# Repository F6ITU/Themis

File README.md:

# Themis

A simple directional coupler

This coupler is based on a "tandem match" design with input compensation capacitor.
 
It should be able to fit any kind of amplifier, from 10 to 150 W

The pcb itself  supports the 2 main toroids of the transformer, input and output coax connectors 
and two coupled outputs.

These outputs are followed by a dual detector located on each branch of the coupler. The detected voltage 
is buffered by a dual rail to rail op amp. The output of the operational amplifier is then 
lowered by a resistive divider that keeps each output below the maximum input voltage of Angelia's ADC 

A optional "raw" FWD output is dedicated to the predistorsion -aka pure signal- feedback

3 different versions have been designed so far : V 1.0 was operational but the design and routing were absolutely ugly, with a crazy stripe-line trace.
V2.0 was a real enhancement of the general design (straight microstrip, simpler shielding). V2.1 offers now some small cleaning of the general design
(pure signal output located on the bottom layer, transformer junction also fixed on the bottom layer, thus enhancing the general insulation and 
offering a slightly better directivity. The attenuator of the P.S. output has a better access, thus simplifying the modification of it's value. 

V2.1 is the master branch since March 1st, 2019, and will stay "as is" as long as a new design is pushed.

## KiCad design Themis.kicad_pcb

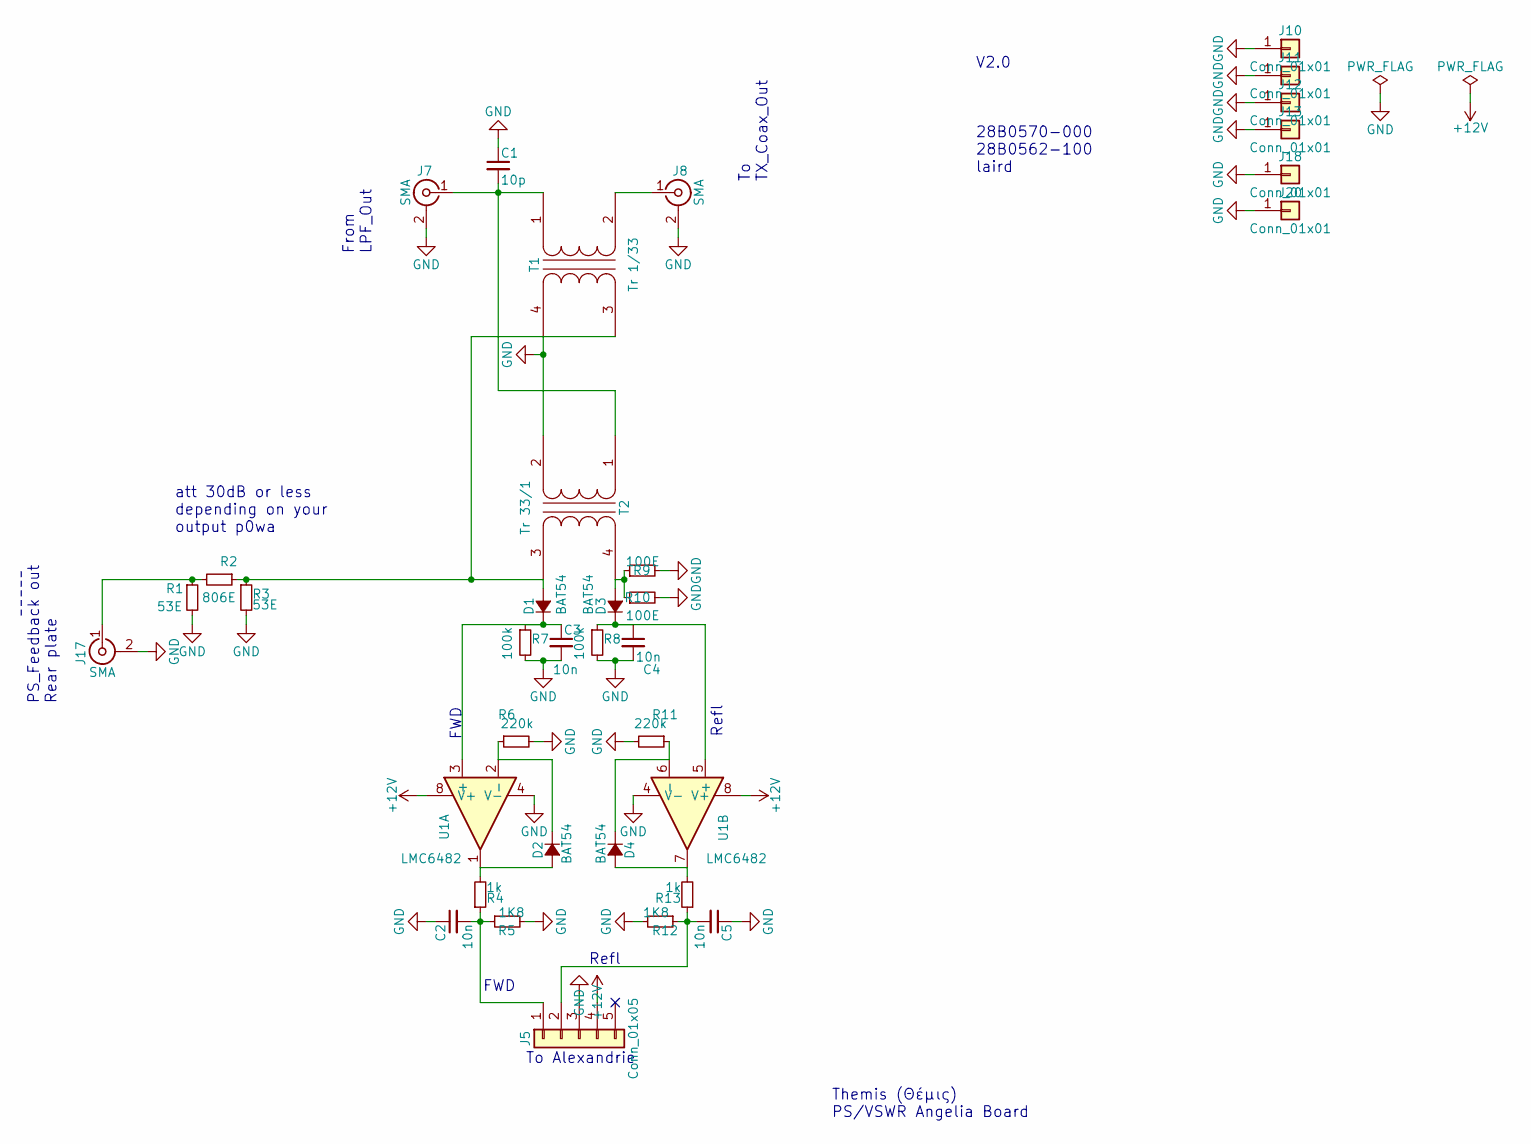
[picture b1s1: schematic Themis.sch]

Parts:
C1: 10p; ATC_500_HandSoldering
C2, C3, C4, C5: 10n; C_0805_HandSoldering
D1, D2, D3, D4: BAT54; D_SOT-23_ANK
J5: Conn_01x05; Molex_KK-6410-05_05x2.54mm_Straight
J7, J8, J17: SMA; SMA_PINS
J10, J11, J12, J13, J18, J20: Conn_01x01; MountingHole_3.2mm_M3_DIN965_Pad
R1, R3: 53E; R_0805_HandSoldering
R2: 806E; R_0805_HandSoldering
R4, R13: 1k; R_0805_HandSoldering
R5, R12: 1K8; R_0805_HandSoldering
R6, R11: 220k; R_0805_HandSoldering
R7, R8: 100k; R_0805_HandSoldering
R9, R10: 100E; R_0805_HandSoldering
T1: Tr 1/33; TR_T50_V_smd
T2: Tr 33/1; TR_T50_H_SMD
U1: LMC6482; SOIC-8_3.9x4.9mm_P1.27mm

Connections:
+12V: J5.4, U1.8 (V+); also elsewhere on the board
GND: C1.1, C2.1, C3.2, C4.2, C5.1, J5.3, J7.2 (Ext), J8.2 (Ext), J10.1, J11.1, J12.1, J13.1, J17.2 (Ext), J18.1, J20.1, R1.2, R3.2, R5.2, R6.2, R7.2, R8.2, R9.2, R10.2, R11.2, R12.2, T1.4 (SB), T2.2 (AB), U1.4 (V-); also elsewhere on the board
unnamed: C1.2, J7.1 (In), T1.1 (AA), T2.1 (AA)
unnamed: C2.2, J5.1, R4.1, R5.1
unnamed: C3.1, D1.1 (K), R7.1, U1.3 (+)
unnamed: C4.1, D3.1 (K), R8.1, U1.5 (+)
unnamed: C5.2, J5.2, R12.1, R13.1
unnamed: D1.2 (A), R2.1, R3.1, T1.3 (SA), T2.3 (SA)
unnamed: D2.1 (K), R6.1, U1.2 (-)
unnamed: D2.2 (A), R4.2, U1.1
unnamed: D3.2 (A), R9.1, R10.1, T2.4 (SB)
unnamed: D4.1 (K), R11.1, U1.6 (-)
unnamed: D4.2 (A), R13.2, U1.7
unnamed: J8.1 (In), T1.2 (AB)
unnamed: J17.1 (In), R1.1, R2.2

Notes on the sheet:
att 30dB or less depending on your output p0wa
Refl
FWD
Themis (Θέμις) PS/VSWR Angelia Board
To TX_Coax_Out
From LPF_Out
To Alexandrie
PS_Feedback out Rear plate
V2.0 28B0570-000 28B0562-100 laird

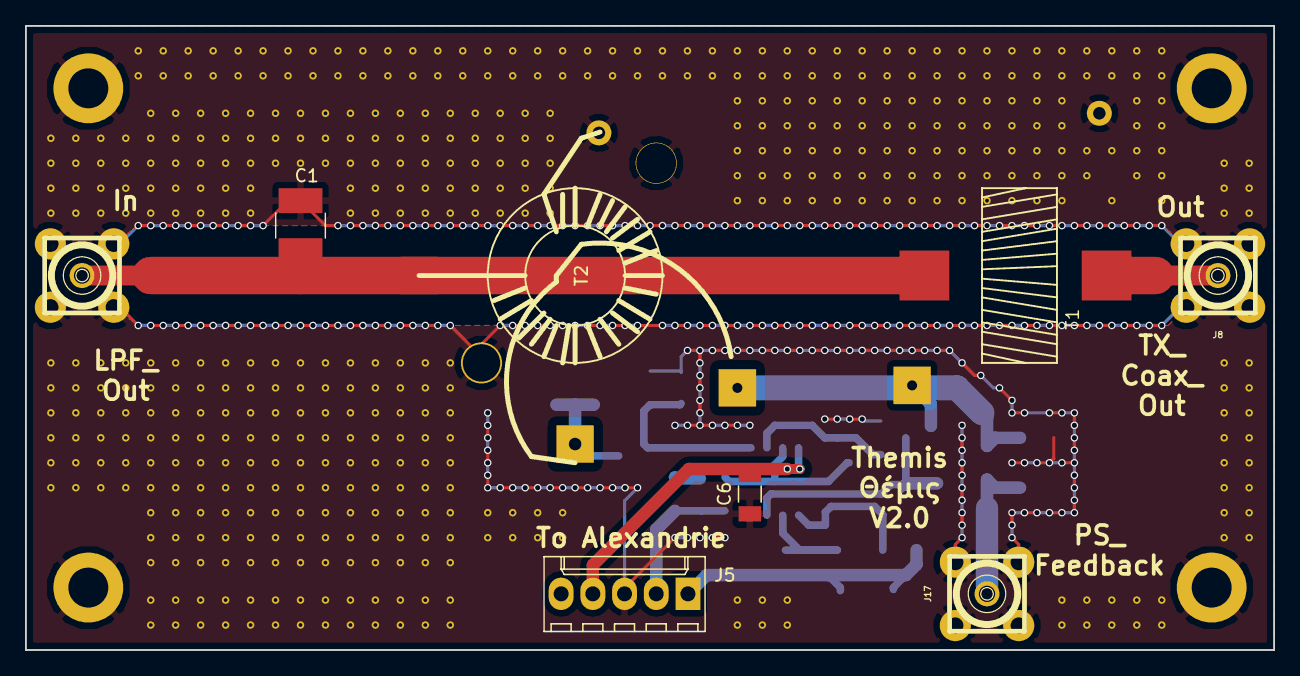
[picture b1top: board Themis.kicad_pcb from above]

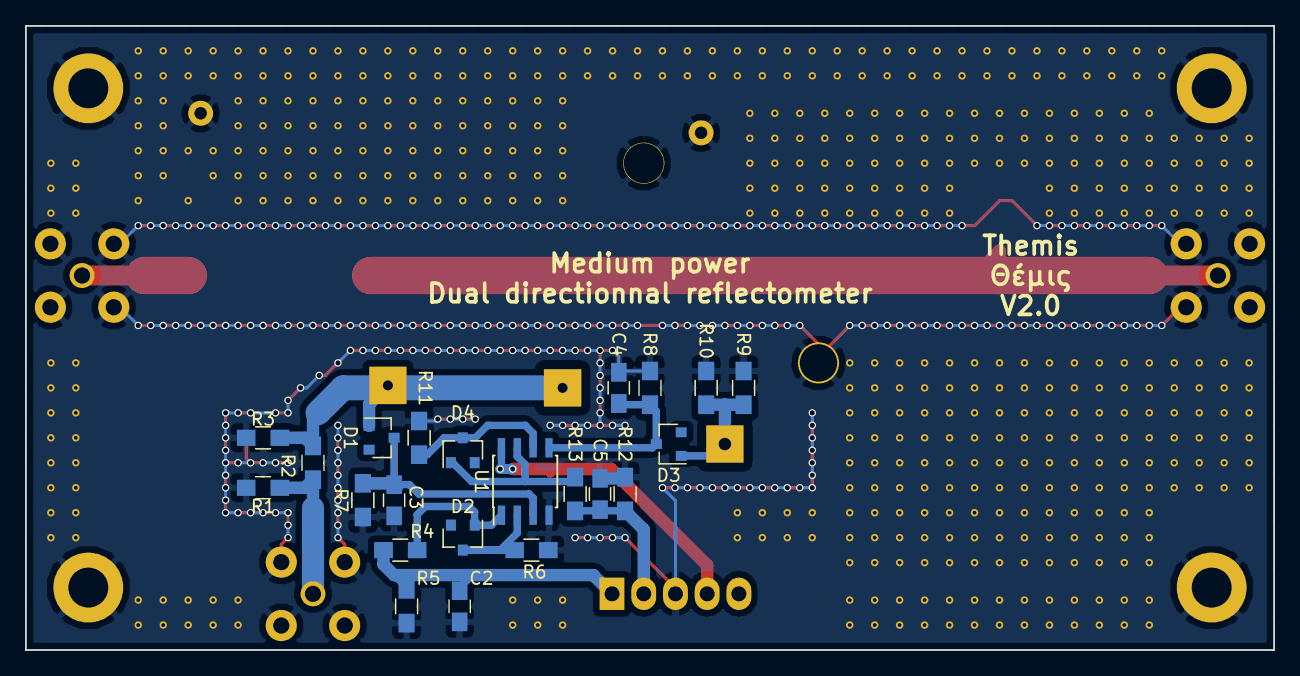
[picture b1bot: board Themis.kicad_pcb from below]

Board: 2 copper layers, 100.0 x 50.0 mm, 36 parts (22 on the bottom side), 15 nets.

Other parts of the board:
C6: 10n; C_1206_3216Metric_Pad1.24x1.80mm_HandSolder

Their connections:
+12V: C6.2; also elsewhere on the board
GND: C6.1; also elsewhere on the board

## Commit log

2018-01-04 first commit of Themis coupler
2018-01-05 BAT54 and transformer shielding added
2018-01-05 via stitching added, new gerber
2018-01-05 silkmask cleaning, new gerber
2018-01-06 new stitching, new gerber
2018-01-14 ajout ss rep
2018-01-14 ajout fichier dans ss rep
2018-01-14 back to normal
2018-01-21 new gerber added
2018-01-22 BOM addded
2018-01-26 enlarged PS_Feedback trace
2018-02-25 minor silk error fixed
2018-03-10 relay references added
2018-03-17 Branch for Themis V1
2018-03-17 README changed
2018-03-17 cleaning V1 repo
2018-03-17 gerber subdir cleaned
2018-07-08 simplified version, no relay
2018-07-15 temporary update
2018-07-15 en route pour la version 2.0
2018-07-19 preparing themis v2
2018-07-19 new README. This branch is deprecated. Use V2 instead
2018-07-23 Themis V2
2018-07-23 Themis V2.0
2018-07-23 new heavy duty stitching
2018-07-24 decoupling cap added in the op-amp power rail
2019-01-02 Attenuator and RF Pure signal out on lower side
2019-01-02 V3, work under progress, do not use as is
2019-03-01 V 2.1, some components switched on the bottom side
2019-03-01 Readme updated
2019-03-15 upgrade to Kicad 5.x
